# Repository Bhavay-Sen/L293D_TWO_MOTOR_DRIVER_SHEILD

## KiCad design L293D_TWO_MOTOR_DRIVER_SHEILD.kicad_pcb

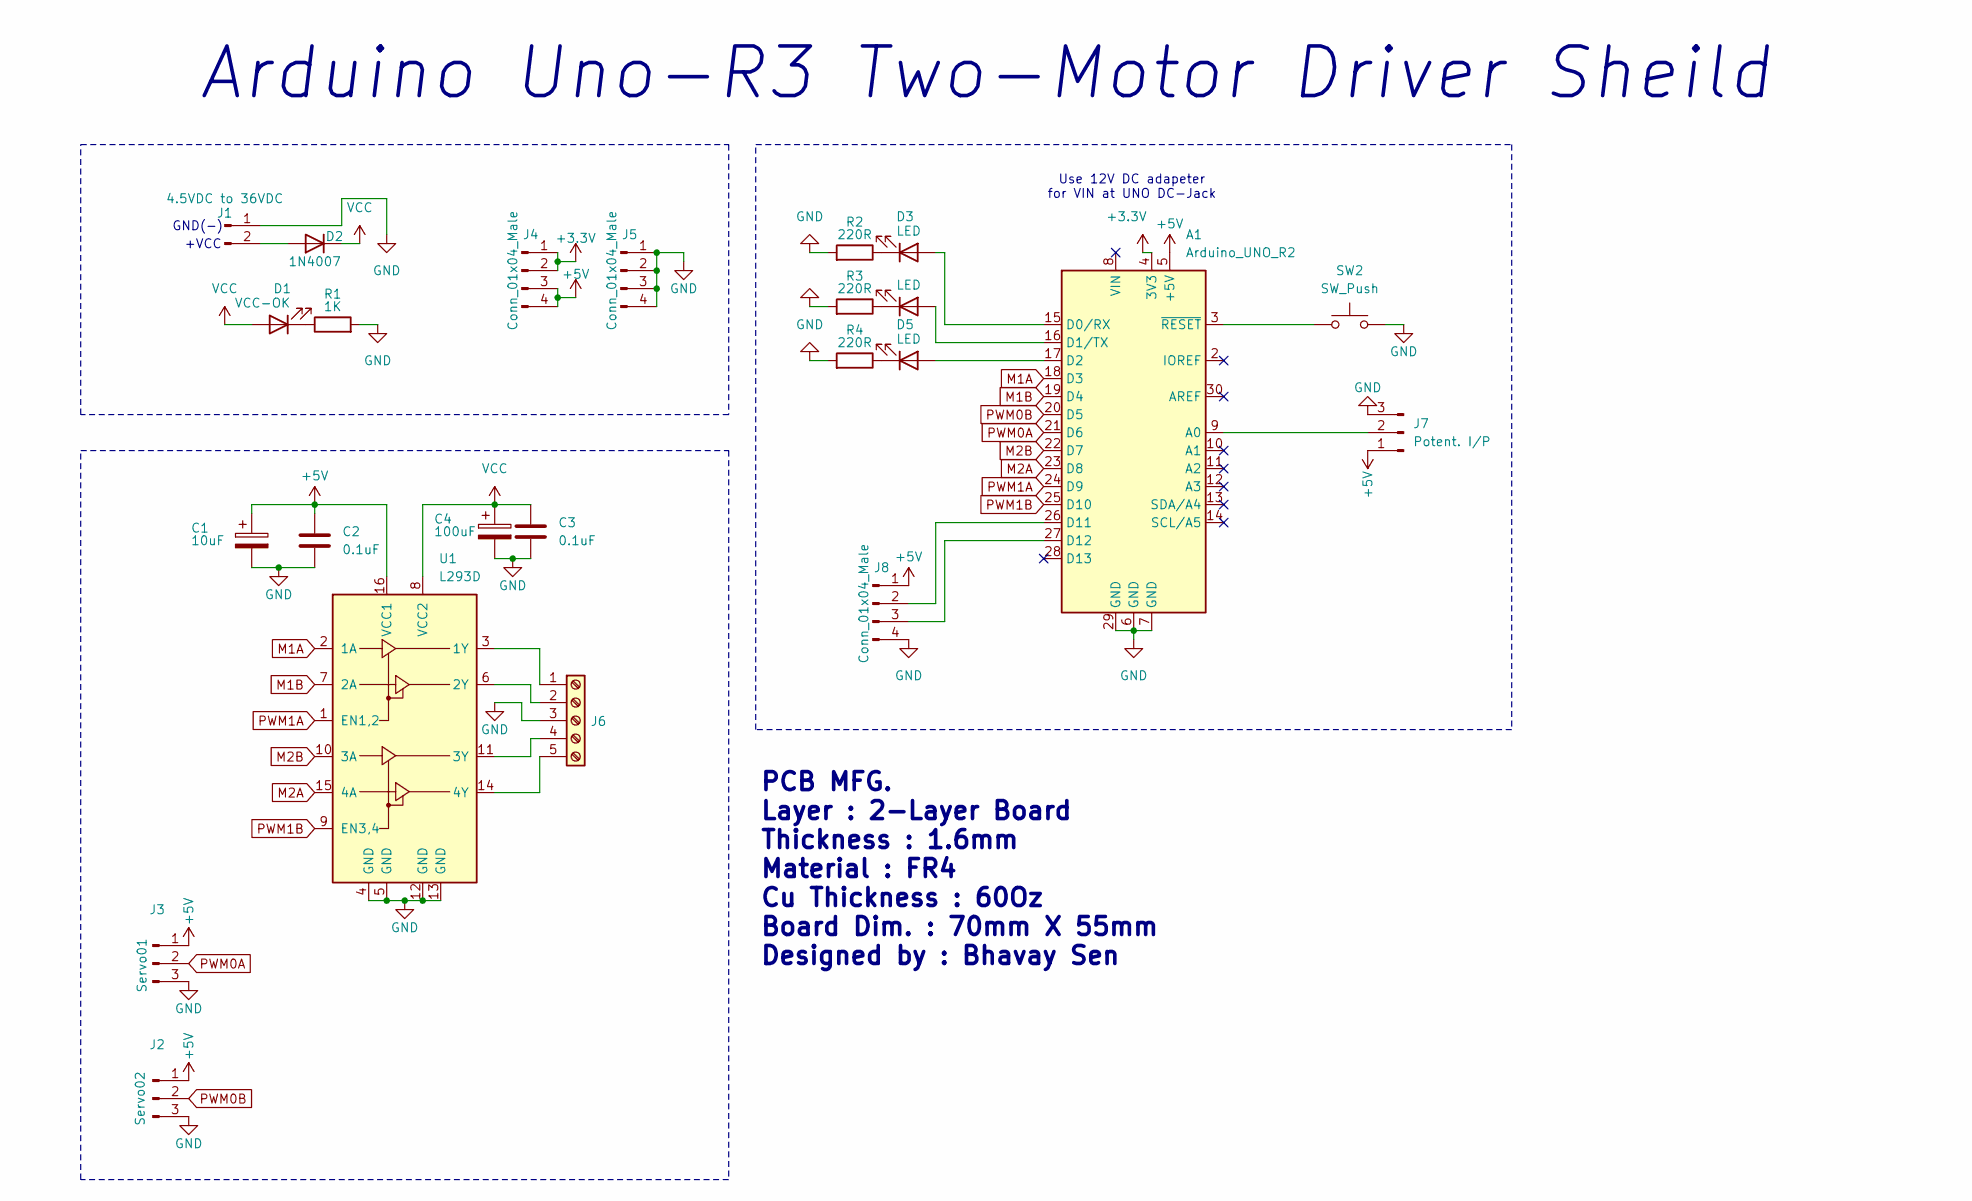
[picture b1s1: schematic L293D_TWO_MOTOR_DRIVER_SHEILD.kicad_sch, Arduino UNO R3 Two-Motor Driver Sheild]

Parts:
A1: Arduino_UNO_R2
C1: 10uF; CP_Radial_D6.3mm_P2.50mm
C2, C3: 0.1uF; CP_Radial_D5.0mm_P2.50mm
C4: 100uF; CP_Radial_D8.0mm_P3.50mm
D1: VCC-OK; LED_D5.0mm
D2: 1N4007; D_DO-41_SOD81_P10.16mm_Horizontal
D3, D4, D5: LED; LED_D5.0mm
J1: 4.5VDC to 36VDC; JST_PH_S2B-PH-K_1x02_P2.00mm_Horizontal
J2: Servo02; PinSocket_1x03_P2.54mm_Vertical
J3: Servo01; PinSocket_1x03_P2.54mm_Vertical
J4, J5, J8: Conn_01x04_Male; PinSocket_1x04_P2.54mm_Vertical
J6: S; TerminalBlock_Phoenix_MKDS-1,5-5-5.08_1x05_P5.08mm_Horizont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
J7: Potent. I/P; JST_XH_S3B-XH-A-1_1x03_P2.50mm_Horizontal
R1: 1K; R_Axial_DIN0207_L6.3mm_D2.5mm_P7.62mm_Horizontal
R2, R3, R4: 220R; R_Axial_DIN0207_L6.3mm_D2.5mm_P7.62mm_Horizontal
SW2: SW_Push; SW_PUSH_6mm_H5mm
U1: L293D; DIP-16_W7.62mm

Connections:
+3.3V: A1.4 (3V3), J4.1, J4.2
+5V: A1.5 (+5V), C1.1, C2.1, J2.1, J3.1, J4.3, J4.4, J7.1, J8.1, U1.16 (VCC1)
GND: A1.6 (GND), A1.7 (GND), A1.29 (GND), C1.2, C2.2, C3.2, C4.2, J1.1, J2.3, J3.3, J5.1, J5.2, J5.3, J5.4, J6.3, J7.3, J8.4, R1.2, R2.2, R3.2, R4.2, SW2.2, U1.4 (GND), U1.5 (GND), U1.12 (GND), U1.13 (GND)
M1A: A1.18 (D3), U1.2 (1A)
M1B: A1.19 (D4), U1.7 (2A)
M2A: A1.23 (D8), U1.15 (4A)
M2B: A1.22 (D7), U1.10 (3A)
unnamed: A1.9 (A0), J7.2
unnamed: A1.15 (D0/RX), D3.2 (A)
unnamed: A1.16 (D1/TX), D4.2 (A)
unnamed: A1.17 (D2), D5.2 (A)
unnamed: A1.26 (D11), J8.2
unnamed: A1.27 (D12), J8.3
unnamed: A1.3 (~RESET), SW2.1
unnamed: D1.1 (K), R1.1
unnamed: D2.2 (A), J1.2
unnamed: D3.1 (K), R2.1
unnamed: D4.1 (K), R3.1
unnamed: D5.1 (K), R4.1
unnamed: J6.1, U1.3 (1Y)
unnamed: J6.2, U1.6 (2Y)
unnamed: J6.4, U1.11 (3Y)
unnamed: J6.5, U1.14 (4Y)
PWM0A: A1.21 (D6), J3.2
PWM0B: A1.20 (D5), J2.2
PWM1A: A1.24 (D9), U1.1 (EN1,2)
PWM1B: A1.25 (D10), U1.9 (EN3,4)
VCC: C3.1, C4.1, D1.2 (A), D2.1 (K), U1.8 (VCC2)

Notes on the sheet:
Arduino Uno-R3 Two-Motor Driver Sheild
GND(-)
PCB MFG. Layer : 2-Layer Board Thickness : 1.6mm Material : FR4 Cu Thickness : 60Oz Board Dim. : 70mm X 55mm Designed by : Bhavay Sen
Use 12V DC adapeter for VIN at UNO DC-Jack
+VCC

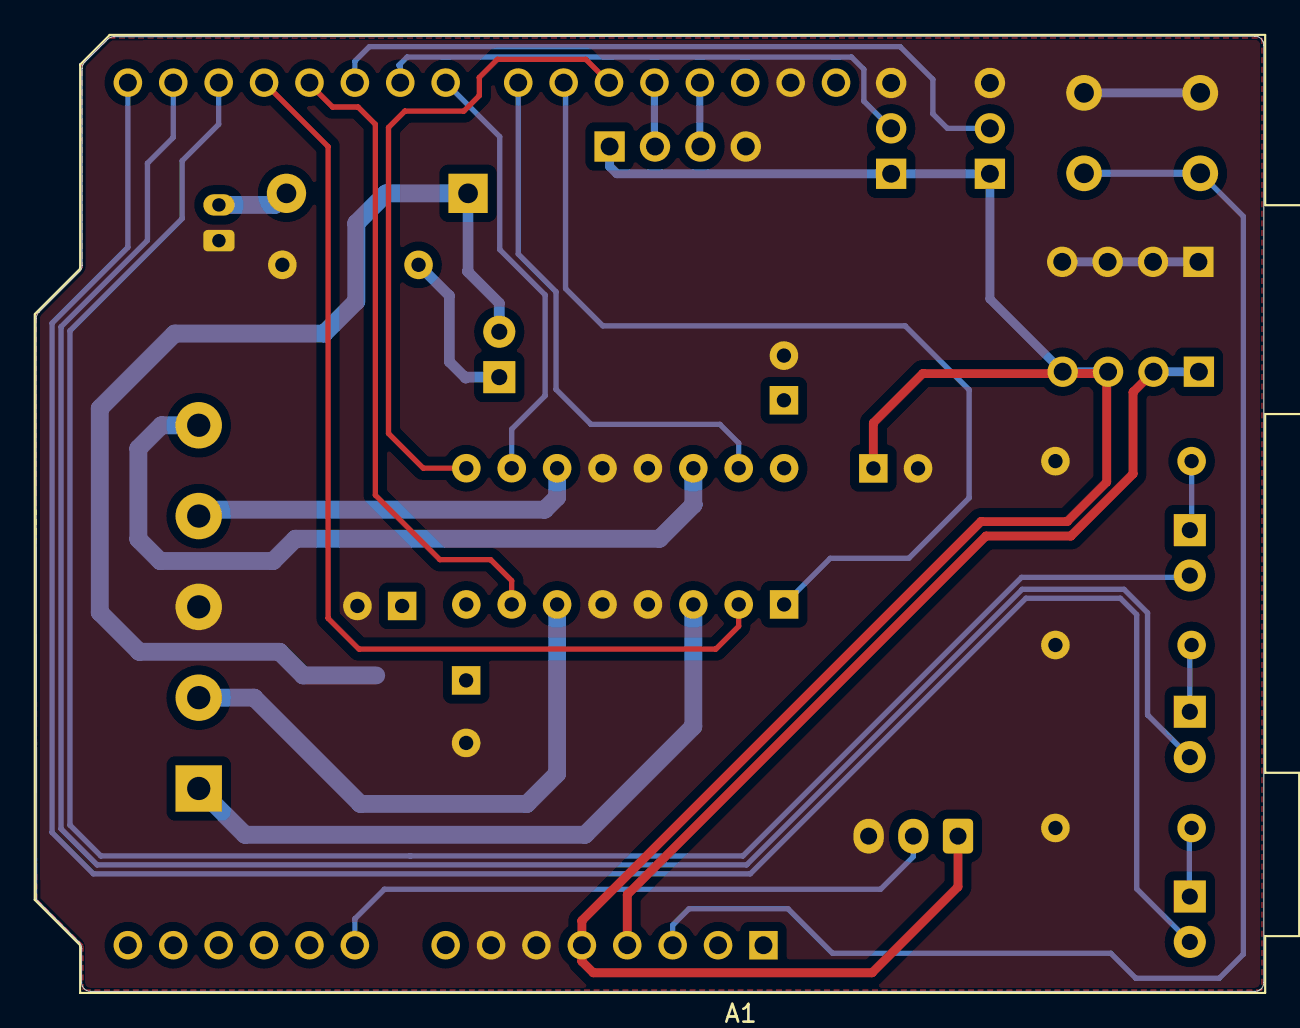
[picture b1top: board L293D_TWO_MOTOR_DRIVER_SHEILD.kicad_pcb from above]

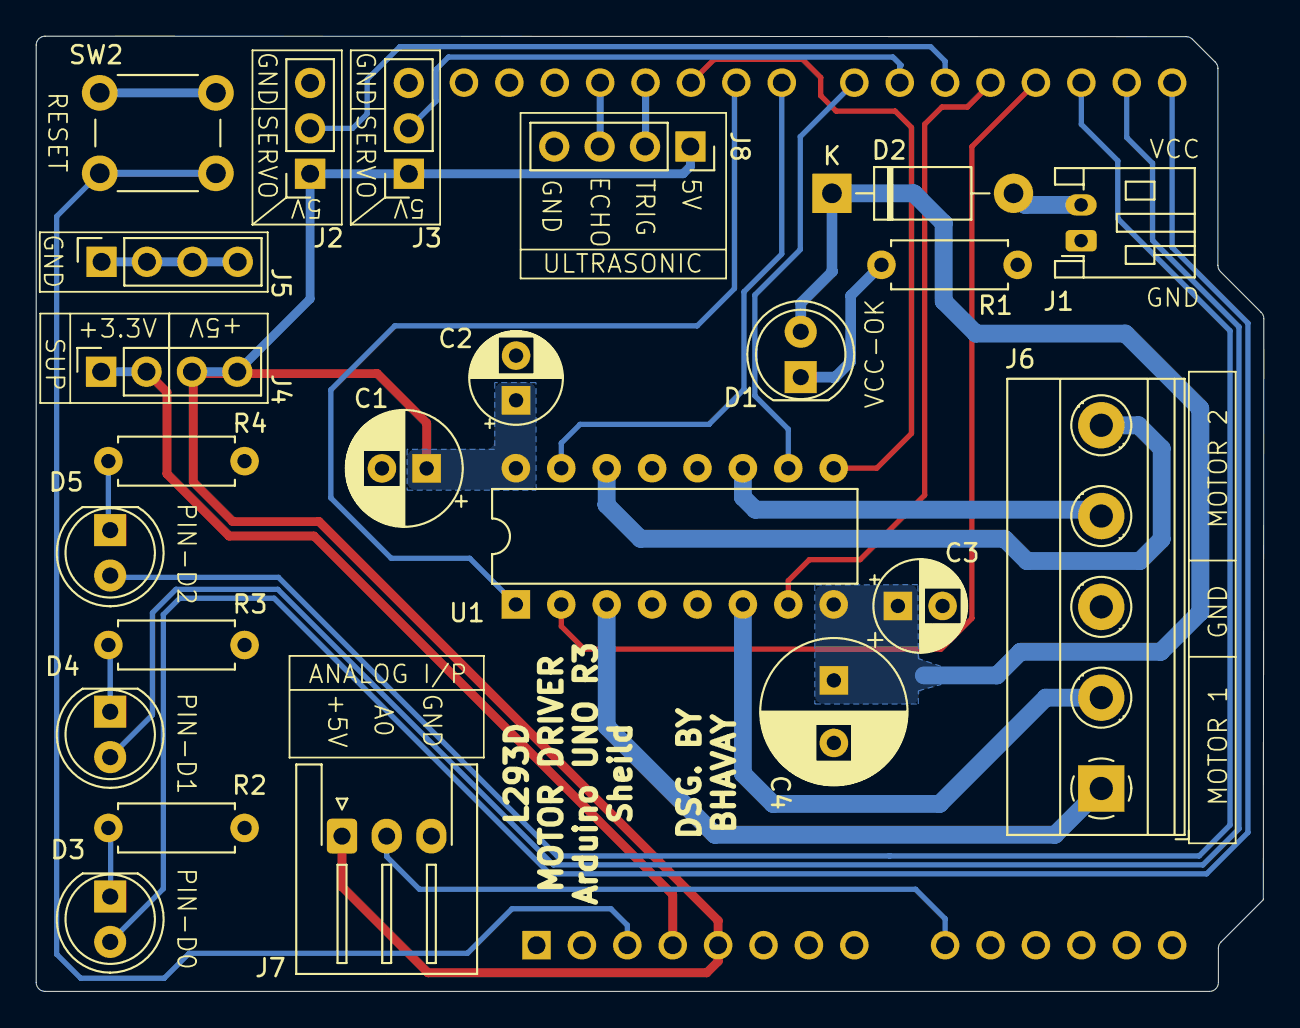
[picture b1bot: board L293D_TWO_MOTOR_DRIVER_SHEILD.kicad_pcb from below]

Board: 2 copper layers, 68.7 x 53.4 mm, 24 parts (23 on the bottom side), 28 nets.

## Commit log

2024-08-04 First commit - Frist version of design completion
2024-08-04 updated LED placement for digital IOs 0,1,2
